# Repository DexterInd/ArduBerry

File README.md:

## **Arduberry**
This project combines the brains of a Raspberry Pi with the brawn of an Arduino.  [Read more about the Arduberry here.](http://www.dexterindustries.com/Arduberry)

These files have been made available online through a [Creative Commons Attribution-ShareAlike 3.0](http://creativecommons.org/licenses/by-sa/3.0/) license.

## Getting Started

We've devoted some serious time to trying to make sure that it's easy to get started.  If you're lost, we would like to first direct you to our [website for the Arduberry] (http://www.dexterindustries.com/Arduberry/)

## This Repository

This repository only holds firmware and hardware designs.  
**Python** - If you're looking for our Arduberry Python libraries, look here:	https://github.com/DexterInd/Arduberry
	
**C** - If you're looking for the Arduberry C Libraries, look here: 		https://github.com/DexterInd/Arduberry
	
**Scratch** - If you're looking for the Arduberry Scratch libraries, look here:	https://github.com/DexterInd/Arduberry

**Script** - If you're looking for the Arduberry Scripts for installing the softwares and other settings on the Raspberry PI, look here:	https://github.com/DexterInd/ArduBerry/tree/master/script

## Quick Install

In order to quick install the `Arduberry` repository, open up a terminal and type the following command:
```
sudo apt-get update # required if debian packages are not yet installed
```
```
curl -kL dexterindustries.com/update_arduberry | bash
```
The same command can be used for updating the `Arduberry` to the latest version.

## Image for the SD Card
Our custom image for the Raspberry Pi makes using the Arduberry easy. You can download the latest image [here.](http://www.dexterindustries.com/howto/raspberry-pi-tutorials/install-raspbian-for-robots-image-on-an-sd-card/)
	
## Firmware
The board firmware is made in Arduino in order to make it super-hackable.  The firmware is written in Arduino 1.0 and can be uploaded directly from the Raspberry Pi itself .

The board supports most of the Arduino sensors and shields and can interact with the Raspberry Pi via I2C and Serial and SPI is used for code burning.

## Pin Description

## Uploading the Code to Arduberry
Select the programmer as "Raspberry Pi GPIO"and Use CTRL + Shift + U to Upload the Code to the Arduberry

[Dexter Industries](http://www.dexterindustries.com/).
[Arduberry.] (http://www.dexterindustries.com/Arduberry)

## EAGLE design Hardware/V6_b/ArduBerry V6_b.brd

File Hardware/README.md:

#Arduberry

The Arduberry combines the brains of a Raspberry Pi with the brawn of an Arduino.   Arduberry for the Raspberry Pi developed by [Dexter Industries.](http://www.dexterindustries.com/Arduberry)  

This folder contains hardware designs for the Arduberry.

## License
These files have been made available online through a Creative Commons Attribution-ShareAlike 3.0 license. Please refer here for more details: http://creativecommons.org/licenses/by-sa/3.0/

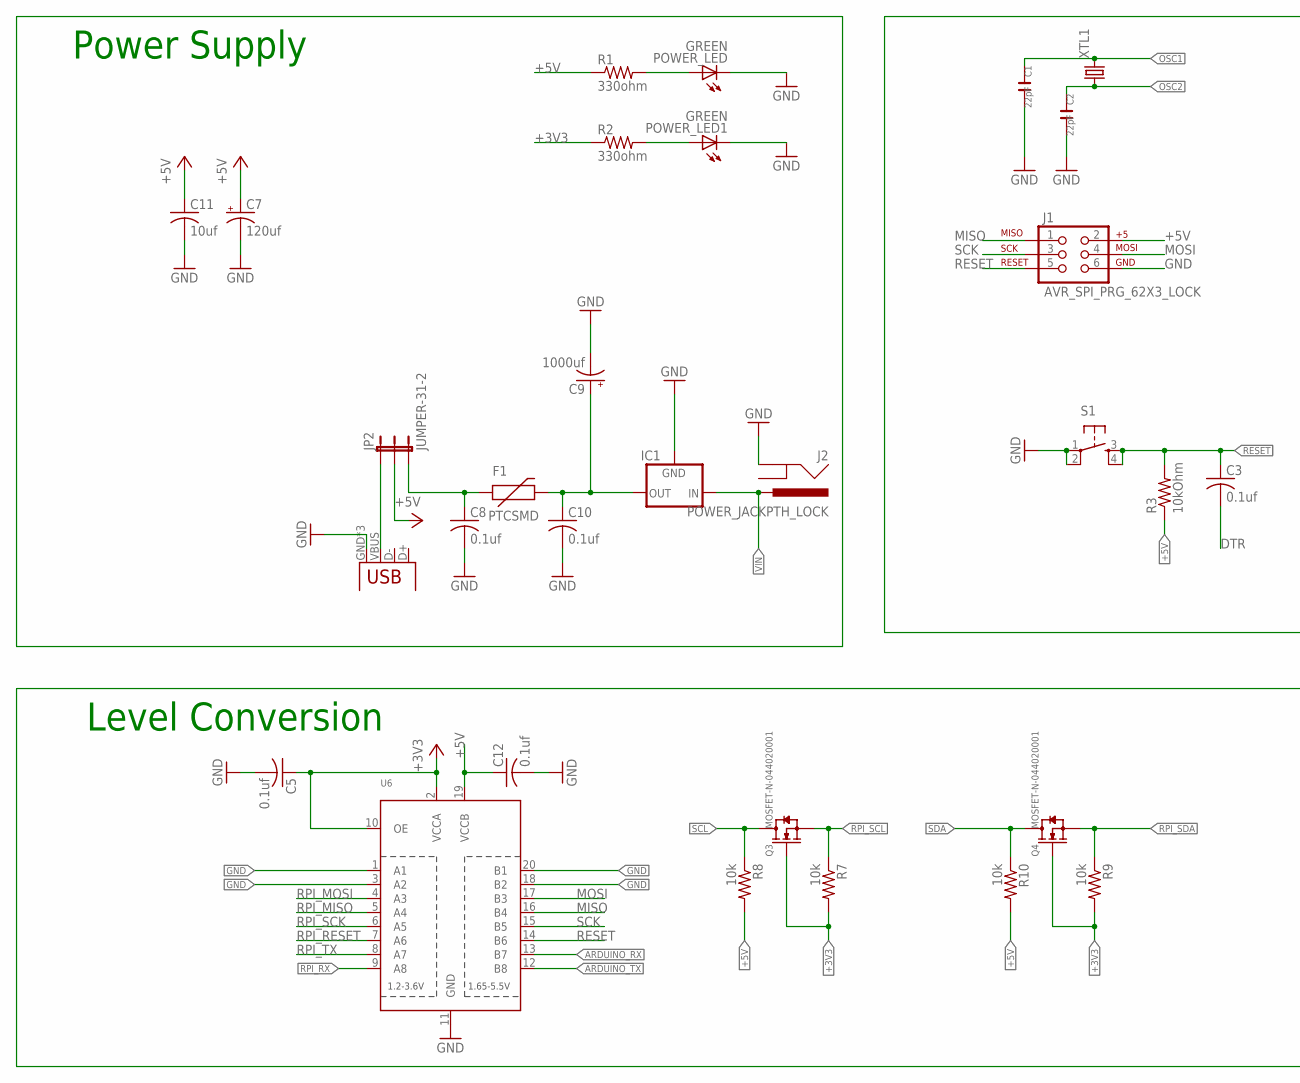
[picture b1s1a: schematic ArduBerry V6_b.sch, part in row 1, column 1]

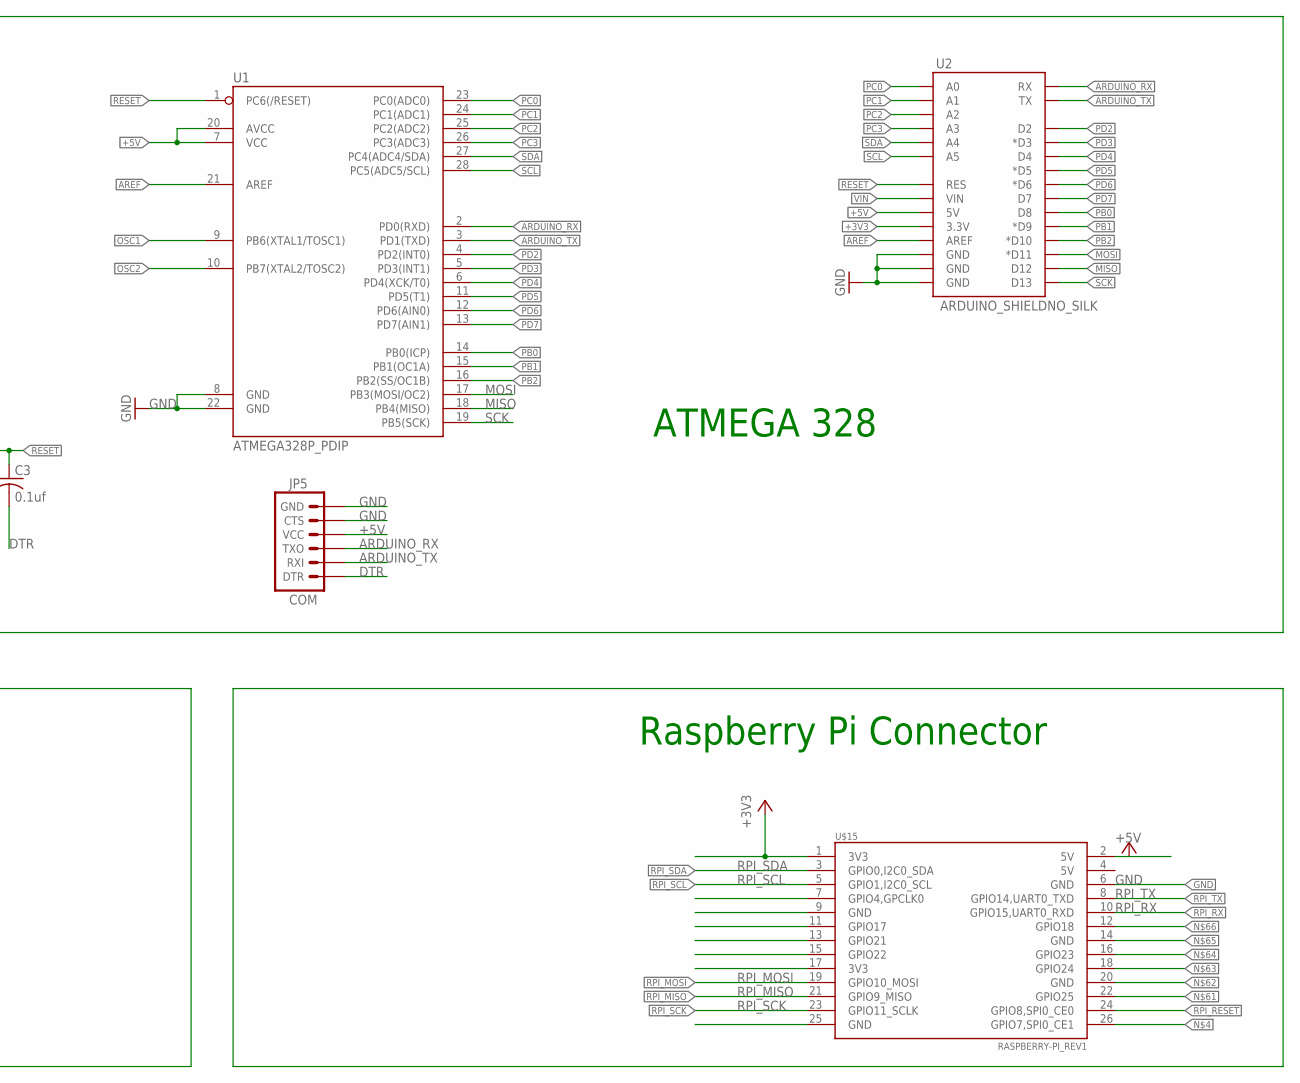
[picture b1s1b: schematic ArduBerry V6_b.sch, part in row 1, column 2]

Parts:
C1, C2: 22pF; C0805
C3, C5, C8, C10, C12: 0.1uf; C0603
C7: 120uf; E2,5-6
C9: 1000uf; E3,5-10
C11: 10uf; C0805
F1: PTCSMD; PTC-1206
IC1: V_REG_78XXSIDE; 78XXL
J1: AVR_SPI_PRG_62X3_LOCK; 2X3_LOCK
J2: POWER_JACKPTH_LOCK; POWER_JACK_PTH_LOCK
JP1: USB-MICROB
JP2: JUMPER-31-2; SJ_3_PASTE1&2
JP5: COM; 1X06
POWER_LED, POWER_LED1: GREEN; LED-0603
Q3, Q4: MOSFET-N-044020001; SOT23
R1, R2: 330ohm; 0603-RES
R3: 10kOhm; 0603-RES
R7, R8, R9, R10: 10k; 0603-RES
S1: TAC_SWITCHPTH; TACTILE-PTH
U1: ATMEGA328P_PDIP; DIL28-3
U2: ARDUINO_SHIELDNO_SILK; DUEMILANOVE_VIAS
U6: TXB0108PWR; TSSOP20
U$15: RASPBERRY-PI_REV1
XTL1: CRYSTALHC49S; HC49/S

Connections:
5V_IN_USB: JP1.VBUS, JP2.1
+3V3: C5.1, Q3.1 (G), Q4.1 (G), R2.1, R7.2, R9.2, U2.3.3V, U6.2 (VCCA), U6.10 (OE), U$15.1 (3V3)
+5V: C7.+, C11.1, C12.1, J1.2, JP2.2, JP5.4 (VCC), R1.1, R3.1, R8.2, R10.2, U1.7 (VCC), U1.20 (AVCC), U2.5V, U6.19 (VCCB), U$15.2 (5V)
ARDUINO_RX: JP5.3 (TXO), U1.2 (PD0(RXD)), U2.RX, U6.13 (B7)
ARDUINO_TX: JP5.2 (RXI), U1.3 (PD1(TXD)), U2.TX, U6.12 (B8)
AREF: U1.21 (AREF), U2.AREF
DTR: C3.2, JP5.1 (DTR)
GND: C1.2, C2.2, C5.2, C7.-, C8.2, C9.-, C10.2, C11.2, C12.2, IC1.GND, J1.6, J2.GND, JP1.GND, JP1.MT1 (GND), JP1.MT2 (GND), JP5.5 (CTS), JP5.6 (GND), POWER_LED.C, POWER_LED1.C, S1.1, S1.2, U1.8 (GND), U1.22 (GND), U2.GND@0 (GND), U2.GND@1 (GND), U2.GND@2 (GND), U6.1 (A1), U6.3 (A2), U6.11 (GND), U6.18 (B2), U6.20 (B1), U$15.6 (GND)
MISO: J1.1, U1.18 (PB4(MISO)), U2.D12, U6.16 (B4)
MOSI: J1.4, U1.17 (PB3(MOSI/OC2)), U2.D11 (*D11), U6.17 (B3)
unnamed: POWER_LED1.A, R2.2
unnamed: POWER_LED.A, R1.2
OSC1: C1.1, U1.9 (PB6(XTAL1/TOSC1)), XTL1.2
OSC2: C2.1, U1.10 (PB7(XTAL2/TOSC2)), XTL1.1
PB0: U1.14 (PB0(ICP)), U2.D8
PB1: U1.15 (PB1(OC1A)), U2.D9 (*D9)
PB2: U1.16 (PB2(SS/OC1B)), U2.D10 (*D10)
PC0: U1.23 (PC0(ADC0)), U2.A0
PC1: U1.24 (PC1(ADC1)), U2.A1
PC2: U1.25 (PC2(ADC2)), U2.A2
PC3: U1.26 (PC3(ADC3)), U2.A3
PD2: U1.4 (PD2(INT0)), U2.D2
PD3: U1.5 (PD3(INT1)), U2.D3 (*D3)
PD4: U1.6 (PD4(XCK/T0)), U2.D4
PD5: U1.11 (PD5(T1)), U2.D5 (*D5)
PD6: U1.12 (PD6(AIN0)), U2.D6 (*D6)
PD7: U1.13 (PD7(AIN1)), U2.D7
REG_OUT: C8.1, F1.1, JP2.3
RESET: C3.1, J1.5, R3.2, S1.3, S1.4, U1.1 (PC6(/RESET)), U2.RES, U6.14 (B6)
RPI_MISO: U6.5 (A4), U$15.21 (GPIO9_MISO)
RPI_MOSI: U6.4 (A3), U$15.19 (GPIO10_MOSI)
RPI_RESET: U6.7 (A6), U$15.24 (GPIO8,SPI0_CE0)
RPI_RX: U6.9 (A8), U$15.10 (GPIO15,UART0_RXD)
RPI_SCK: U6.6 (A5), U$15.23 (GPIO11_SCLK)
RPI_SCL: Q3.2 (S), R7.1, U$15.5 (GPIO1,I2C0_SCL)
RPI_SDA: Q4.2 (S), R9.1, U$15.3 (GPIO0,I2C0_SDA)
RPI_TX: U6.8 (A7), U$15.8 (GPIO14,UART0_TXD)
SCK: J1.3, U1.19 (PB5(SCK)), U2.D13, U6.15 (B5)
SCL: Q3.3 (D), R8.1, U1.28 (PC5(ADC5/SCL)), U2.A5
SDA: Q4.3 (D), R10.1, U1.27 (PC4(ADC4/SDA)), U2.A4
VIN: IC1.IN, J2.PWR, U2.VIN
VIN_5V: C9.+, C10.1, F1.2, IC1.OUT

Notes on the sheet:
Power Supply
Level Conversion
Raspberry Pi Connector
ATMEGA 328

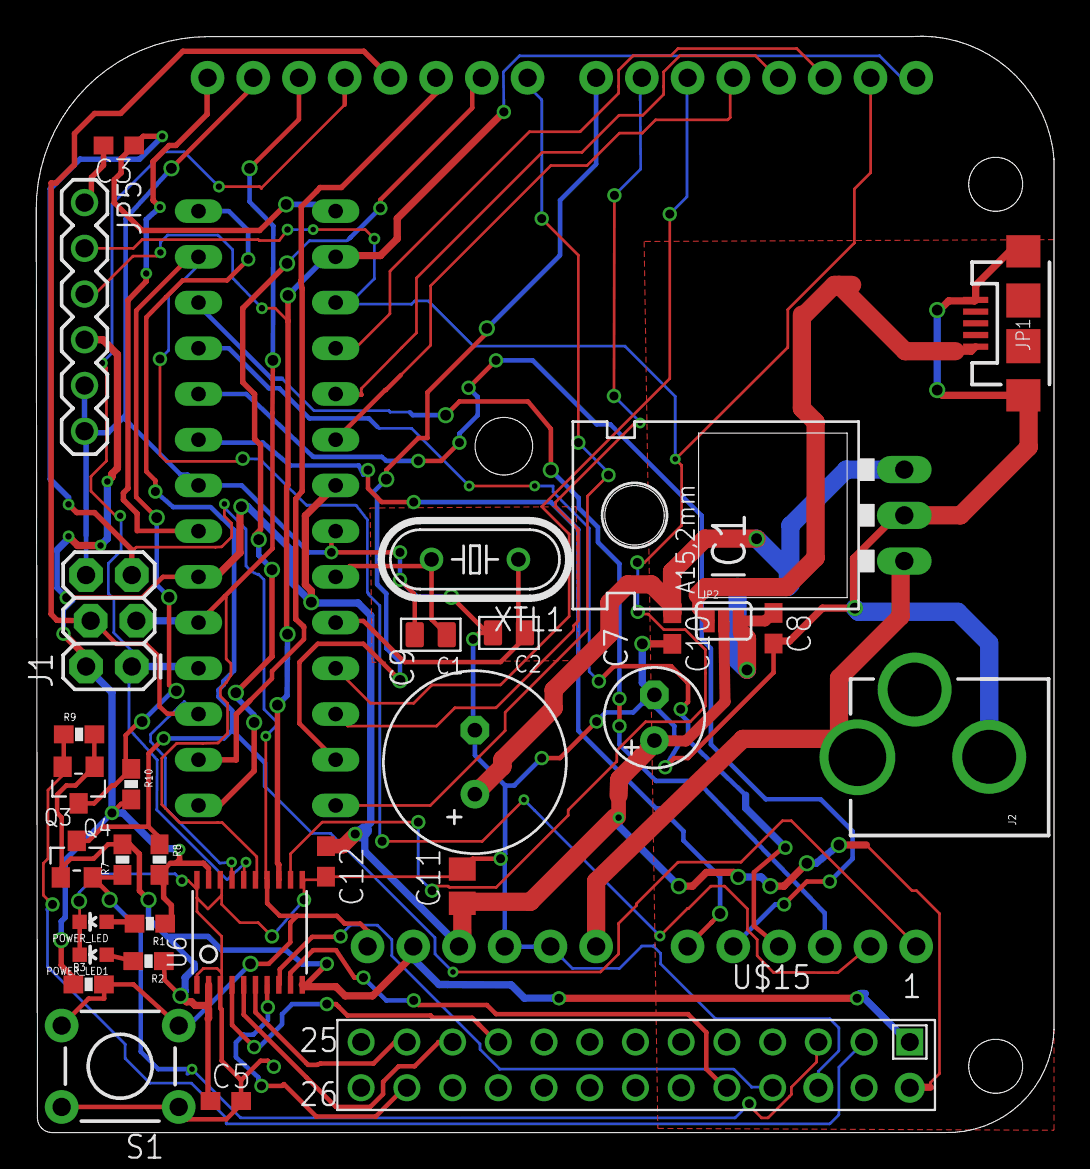
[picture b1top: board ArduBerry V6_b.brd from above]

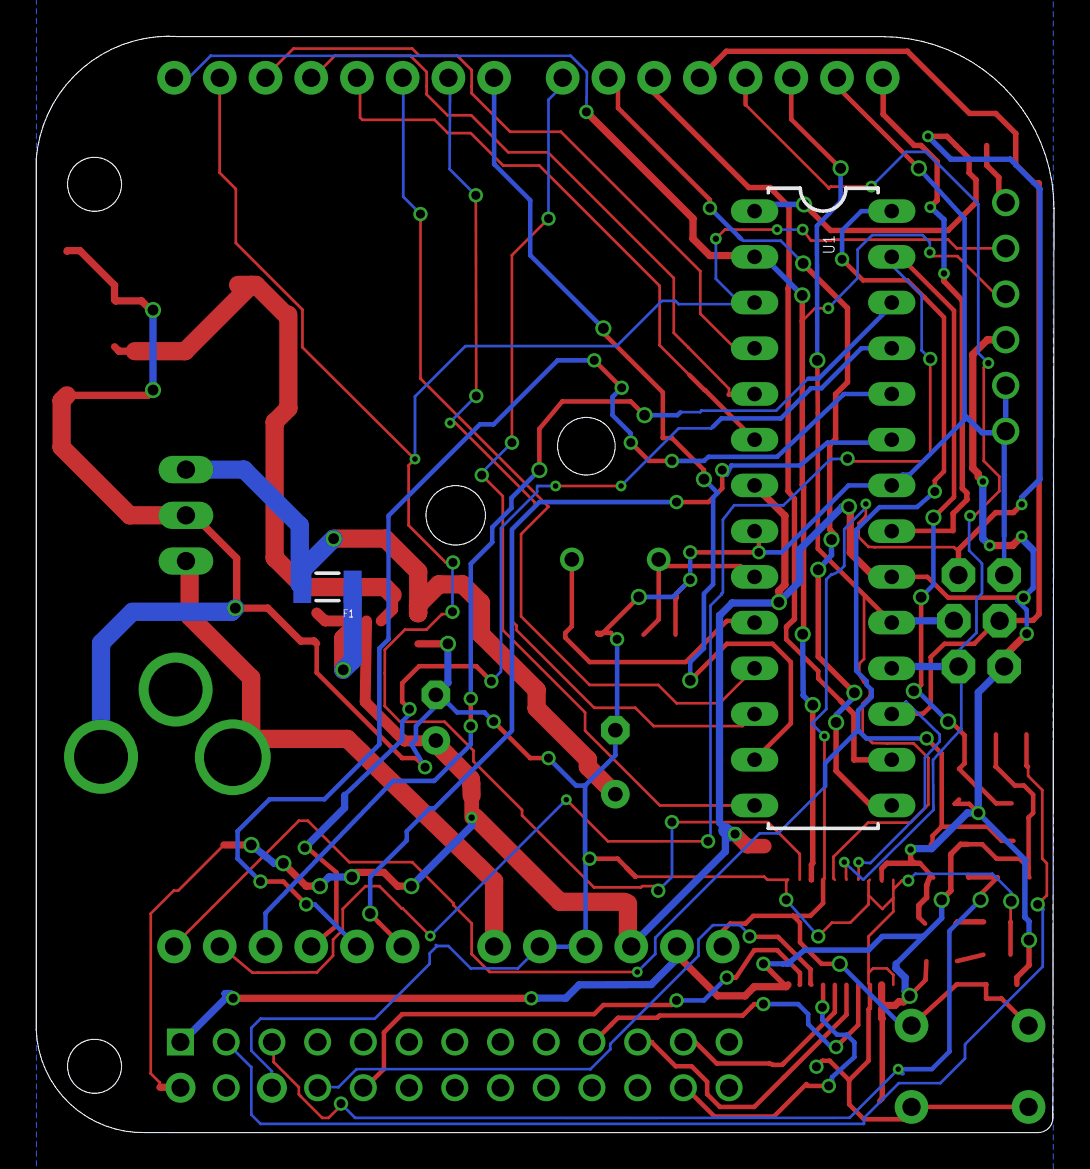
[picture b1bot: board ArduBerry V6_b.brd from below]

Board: 2 copper layers, 56.5 x 60.9 mm, 34 parts (2 on the bottom side), 42 nets.

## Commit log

2013-12-03 Uploading Hardware and Readme - First commit
2013-12-06 Changes made for prototype 2
    -jumpers removed
    -mosfets changes
    -capacitor position changed
    -reset button changed from smd to dip
2013-12-20 Rounded the edges
    Rounded the edges of the board a bit. Looks nicer.
2014-01-03 getting started script added
2014-01-04 Install script added
2014-01-09 Serial terminal config added
2014-01-09 Update Documentation
    Added pdf of schematic.
2014-01-09 Changed the levels showing.
2014-01-10 Readme
2014-01-10 Readme?
2014-01-10 Revert "Readme?"
    This reverts commit 4f2af2136bc82451528f52284b3a7bb0edb73228.
2014-01-10 Updated readme and hardware organization
2014-01-10 Added Print of Schematic
2014-01-15 Arduberry Hardware Description picture added
2014-01-16 Add install header
2014-01-16 Update Script
2014-01-17 Updated script install.
2014-01-20 Code for Dixie project added
2014-01-30 PCB_v5 added
    -Added 3.3v LED
    -Changed the V_Reg footprint to LM7805 through-hole
    -Minor changes to the silk_screen
2014-01-30 DRC and Spacing Issues Fixed
2014-05-07 upload image added
2014-05-07 Updated icon link
2014-05-07 upload image updated
2014-05-23 C & python program to communicate with Arduberry
2014-07-18 New hardware iteration started
2014-07-18 Hardware revision complete
    - FTDI connector added
    - Holes for Raspberry Pi Model B+ added
    - Minor changes to silk
2015-02-10 Add lionel train control example
    Added lionel train control example for the Rasberry Pi.
2015-02-10 Adding the web code for lionel train control
    Example web code for lionel train code with the Raspberry Pi.
2015-02-10 lionel-train-switch-control-with-a-raspberry-pi
    Adding some documentation in the python and a readme.
2015-02-10 Add a picture
2015-02-10 Picture attempt 2.
    Trying again.
2015-02-10 Updated readme again.
2015-02-10 Control changes.
2015-07-23 Update Install Scripts
    Internet Connectivity was a problem. Now it's not.
2015-08-19 Update the readme.
2015-08-19 REadme work.
2015-08-19 Cleaning up Readme.
2015-08-20 Update ARduberry script to not restart.
    Arduberry script gives the user the ability to restart now. Or not.
2015-08-20 No auto restart.
    remove auto restart.
2015-08-20 Remove input.
2015-10-07 Update the install script, autorun.
2016-01-11 Arduberry Hardware design files updated
2016-05-05 Arduino IDE opened as root so that serial port is available in IDE
2016-08-29 Adding script
2016-08-29 Changed
2016-08-29 Change again
2016-08-29 Change
2016-08-29 yes accept
2016-09-08 Final changes
    Deleted the commented lines
2016-09-26 wget --output-document=/dev/null
    avoid orphaned index.html files
2016-10-06 Script to select the Arduino install file
2016-10-06 Select Arduino install files
2016-10-07 Updates to install scripts
    Few changes to differentiate between it being run by DI_update and
    direct install
2016-10-07 ArduBerry Banner and a missing if in install_jessie.sh
2017-01-04 wheezy install script updated
    - all repos moved to DI repos on github
    - functions added
2017-01-04 wheezy script cleaned up for merging with jessie
2017-01-04 cleaned up jessie script added
2017-01-04 programmer.txt update added
2017-01-04 avrdude 5.1 installation added
2017-01-04 install sequence updated
2017-01-05 Copy updated programmers.txt for Arduino IDE
    - Adds GPIO programmer support
2017-01-05 rules file added for Serial port access to Arduino
2017-01-05 Install.sh readme updated
2017-01-05 Arduino IDE invocation moved to sudo from gksu
2017-01-05 Install.sh updated to run on both wheezy and Jessie
2017-01-05 Avrdude install sequence changed and gksu removed
2017-01-05 Sudo added to arduino exec to access serial port
2017-01-05 individual jessie and wheezy scripts archived
2017-01-05 Documentation updated
2017-01-10 Install avrdude and wiringpi from script_tools
2017-01-10 Install script filepath updated
2017-01-10 Scripts updated to call functions rather than run scripts
2017-01-12 cosmetic changes to avoid harmless errors and noise from being displayed to the user
2017-01-12 add curl statement at toop
2017-01-12 Arduberry script cleanup
    - Script uses functions from script_tools
    - More feedback
    - Arduino IDE now checks if it already exists and then only installs
    (much faster now)
2017-03-02 Enabling Serial communication
2017-03-02 Shebang and Reference
2017-09-26 Skipping SSL checks on install command in README
2017-09-26 ref RobertLucian/Arduberry#1 : feature - added update fetcher from R4R
2017-09-26 ref RobertLucian/Arduberry#1 : feature - removed "script" folder
2017-09-26 ref RobertLucian/Arduberry#1 : feature - added "Script" folder
2017-09-26 ref RobertLucian/Arduberry#1 : feature - updated README in the script folder
2017-09-26 ref RobertLucian/Arduberry#1 : feature - changed paths accordingly
2017-09-26 ref RobertLucian/ArduBerry#1 : feature - used new Script folder for updater
2018-06-11 hotfix - make installer work again with script_tools & on stretch
2018-06-11 hotfix - keep the same intention, but make it faster
2018-06-12 hotfix - make arduino work for stretch
2018-06-12 hotfix - add command to set arduino for stretch
2018-06-12 hotfix - syntax error on if/elif/else condition
2018-06-12 hotfix - further things on the if statement + echoes
2018-06-12 hotfix - add a comment regarding the Arduino IDE
2018-06-12 hotfix - install script for stretch (#28)
    * hotfix - make installer work again with script_tools & on stretch
    * hotfix - keep the same intention, but make it faster
    * hotfix - make arduino work for stretch
    * hotfix - add command to set arduino for stretch
    * hotfix - syntax error on if/elif/else condition
    * hotfix - further things on the if statement + echoes
2018-06-12 Update README.md (#29)
2018-06-12 Update install.sh (#30)
2018-08-20 hotfix - add a little note about debian packages
2018-08-20 hotfix - changes to install readme
2018-08-20 hotfix - add a little note about debian packages (#31)
    * hotfix - add a little note about debian packages
    * hotfix - changes to install readme

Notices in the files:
parts and their libraries:
zz SparkFun: Licensing: CC v3.0 Share-Alike You are welcome to use this library for commercial purposes.
